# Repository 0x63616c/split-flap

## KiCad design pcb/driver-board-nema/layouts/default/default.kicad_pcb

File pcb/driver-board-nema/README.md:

# split-flap driver board v2 — NEMA 14 / TMC2209

Single-module driver for the split-flap: a socketed **Seeed XIAO ESP32-C6**
drives a socketed **TMC2209 SilentStepStick**, which drives a 4-lead bipolar
**NEMA 14** (0.6 A/phase, 1.8°). The whole module — motor, logic and hall
sensor — runs from **one 12 V barrel jack**.

62 × 76 mm, 2-layer, 1.6 mm FR4. Fits behind a module with room to spare
(the unit plate is 95 × 118 mm).

v1 (`../driver-board/`) is the 28BYJ-48 board — it drove a ULN2003 off USB 5 V.
This is a separate design, not a revision of it. (v1 has had exactly one change
made to it since: its XIAO socket was the same male-header part as this board's
was, and was swapped for a female receptacle.)

## Pinout

XIAO pin assignment is the one `firmware/micropython-spike/tmc_spin.py`
already uses. The hall wiring is carried over from the v1 bench, with a 1 kΩ
series resistor added.

| XIAO | Signal | Goes to |
|---|---|---|
| D0 | STEP | StepStick pin 10 |
| D1 | DIR | StepStick pin 9 |
| D2 | EN | StepStick pin 16 (active **low**; the module pulls it up, so the driver is off until firmware drives it) |
| D6 | PDN_UART | StepStick pin 11, through a 1 kΩ series resistor (R8) |
| D7 | PDN_UART **read** | the same net as D6. D7 is GPIO17 = U0RXD, so the UART can be read as well as written |
| D8 | HALL DO | J1 pin 3, through a 1 kΩ series resistor (R9) |
| 5V | +5 V in | fed **by the on-board buck** through D2, not by USB |
| 3V3 | +3.3 V out | StepStick VIO — this is what sets the driver's logic level |

D3/D4/D5/D9/D10 are socketed but unrouted.

> **The hall line floats when no magnet is present.** An open-collector
> output is high-Z when it is not pulling down, and nothing on this board
> pulls it up. Firmware **must** enable the XIAO's internal pull-up on D8 or
> it will read noise.

### StepStick socket (J5 = pins 9–16, J4 = pins 1–8)

Pin numbering follows the Trinamic *TMC2209 SilentStepStick* hardware manual
(doc rev 1.20). Note this is **not** the naive A4988 column order — the coils
are on the same side as VM, and the header does not carry DIAG or INDEX (those
are module pads 17/18).

```
J4 (pins 1-8)   GND  VIO  M1B  M1A  M2A  M2B  GND  VM
J5 (pins 9-16)  DIR  STEP PDN  UART SPRD MS2  MS1  EN
```

MS1, MS2 and SPREAD are tied to GND: UART address 0 and StealthChop.
Microstepping and run current are set over UART, not by jumpers.

Pin 12 (UART) is left unconnected. The reason is **not** that the module has
its own series resistor on it — it does not; the SilentStepStick fits a 20 kΩ
**pull-down** (R1) there. The reason is that pins 11 and 12 are the two ends
of the module's 3-way solder jumper JMP, and our 1 kΩ (R8) already provides
the series resistance the single-wire UART needs. Driving both ends would
just fight the jumper.

> ### ⚠ Bridge JMP to PDN before UART will do anything
>
> The SilentStepStick ships with **neither** side of JMP bridged: JMP.1 goes
> to pin 11 (PDN) and JMP.3 to pin 12 (UART), and out of the factory the pad
> is open. Until you bridge JMP to the **PDN** side, the driver never sees
> anything the XIAO sends — it silently runs STEP/DIR at its default 1/8
> microstep with the current set by the on-board trim pot, and every UART
> write is a no-op with no error.

### Connectors

| Ref | Type | Pinout (left → right as silkscreened) |
|---|---|---|
| J3 | 5.5 × 2.1 mm barrel, 3 A | **centre positive**, 12 V — **meter tip/sleeve before first power-up**, see below |
| J2 | JST-XH 4-pin, right angle | `A2 A1 B2 B1` — the connector is rotated, hence the reversed order. Labels follow the **driver's** coil naming: on a SilentStepStick M1 is coil B and M2 is coil A, so J2's `A` pair goes to the driver's M2 |
| J1 | JST-XH 3-pin, vertical | `5V GND DO` |

> **Meter J3's tip and sleeve before you apply 12 V.** DC-005 pad numbering is
> not standardised between vendors, and the two pads of the rear row are
> geometrically identical, so there is nothing to tell them apart by eye. The
> pin functions in `parts/DC_005C/DC_005C.ato` are derived by structural
> correspondence with the previous jack, not read off a datasheet — sound
> reasoning, but still an inference. Put a meter on a plugged-in barrel
> connector and confirm tip → J3 pad 1 and sleeve → J3 pad 2 first.

## Power

```
12V jack ──> Q1 (P-FET reverse-polarity gate) ──> +12V rail
                                                   ├─> StepStick VM  (C6 470uF + C7 22uF + C10 100nF)
                                                   └─> U1 TPS563201 ──> +5V ─┬─> hall sensor
                                                                             └─> D2 ──> XIAO 5V pad
XIAO 3V3 out ──> StepStick VIO
```

**Budget** — a 12 V ≥ 2 A brick covers it with margin:

| Load | Draw |
|---|---|
| Motor, 2 phases × 0.6 A into the coils | ~6–9 W → **0.5–0.75 A** at 12 V (coil resistance not in the listing; assumed 8–12 Ω — measure it) |
| XIAO ESP32-C6 (WiFi peaks) | ~0.5 A at 5 V → ~0.25 A at 12 V |
| Hall module | ~20 mA at 5 V |
| **Total** | **~1.0–1.3 A at 12 V** |

J3 is a DC-005C-20A, rated **3 A**. The 1 A-rated DC-005 this board first used
was at or over its limit continuously against that budget.

**VM bulk.** C6 is 470 µF / 25 V with 80 mΩ ESR and an 850 mA ripple rating,
sitting directly beside the StepStick's VM pin, with a 22 µF ceramic (C7)
alongside it for the mid-band and a 100 nF (C10) 2.5 mm from the VM pad itself
for the high-frequency edge — neither of the larger parts is a short at the
tens-of-MHz edges the TMC2209's gate drive puts on VM. The TMC2209 chops the
full coil current out of VM; undersizing this is the classic way to kill the
driver.

**Reverse polarity.** Worth it — barrel bricks vary and the TMC2209 does not
survive reverse VM. A high-side P-FET rather than a series Schottky: the diode
would drop ~0.4 V and burn ~0.4 W at 1 A, and eat the buck's headroom, where
the FET is ~50 mΩ (≈50 mV).

*Orientation.* A P-FET's body diode conducts **drain → source**, so for this to
block on reverse input the drain has to face the jack and the source the
protected rail — which is how Q1 is wired. Getting it the other way round is
not a no-op, it quietly defeats the whole circuit: with the source on the jack
side the body diode's anode faces the load, stays forward-biased under reverse
input, and conducts anyway, putting roughly **−11.3 V** across C6. An earlier
revision of this board had exactly that.

*Gate.* Not tied to GND — the AO3401A is only rated V<sub>GS</sub> ±12 V, which
a 12 V brick sits right on. R5/R6 (100 k/56 k) hang off the **source** (the
gate is referenced to the source, so the divider follows that pin) and park the
gate at 0.64 × V<sub>source</sub> below it: −7.7 V at 12 V in, −9.6 V even at a
15 V brick. Fully enhanced, safely inside the rating. On power-up the body
diode pulls the rail to V<sub>in</sub> − 0.7, which is what gives the divider a
live source to work from; the drop then collapses to I × R<sub>DS(on)</sub>.

**Buck.** TPS563201, 4.5–17 V in, 3 A, D-CAP2 — no external compensation and
no catch diode. V<sub>out</sub> = 0.768 × (1 + 54.9 k/10 k) = **4.99 V**.

*Cff.* R3 carries a 100 pF C0G in parallel (C9). A high-V<sub>out</sub> D-CAP2
converter on an all-ceramic output has very little phase margin at crossover;
TI's SLVAF45, *Why We Need Cff in High Output Voltage D-CAP2/3 Converter for
Stability*, works this exact 12 V → 5 V case and measures phase margin going
from **17.2° to 75.4°** once Cff is fitted. The 54.9 k/10 k pair is TI's from
that note, which is why it is 54.9 k and not 56 k.

*Output capacitance.* TI's stable window is 20–68 µF **effective**. A 22 µF
25 V X5R 0805 loses roughly half its value to DC bias at 5 V, so the two caps
this board originally carried gave ~20–24 µF — sitting on the floor of the
window with tolerance and temperature able to push it under. There are now
three (C3/C4/C8), for ~30–36 µF derated.

*EN.* A plain 100 k pull-up to the 12 V rail. Earlier revisions fitted a
100 k/56 k divider justified as a level-shift for a 6 V abs-max on EN; that
was wrong — SLVSD90B rates EN at abs-max **19 V**. It was not a useful UVLO
either (it releases at V<sub>in</sub> ≈ 3.3 V, below the part's own 4.5 V
minimum), so the low side is gone.

**Trace widths.** Motor coils, the 12 V spine and VM run at 1.0 mm; 5 V and
the buck power nets at 0.8 mm (0.6 mm where they escape the SOT-23-6); logic
at 0.4 mm. 1.0 mm on 1 oz outer copper carries ~2.5 A at a 10 °C rise, against
a ~0.85 A peak coil current.

**12 V and USB together.** The XIAO ESP32-C6's 5V pad is the *same net* as its
USB VBUS, with no series diode anywhere on the module (Seeed schematic v1.0).
Wired straight through, plugging in USB while 12 V was applied would have the
buck driving the host PC's VBUS rail backwards down the cable. **D2**, a
B5819W Schottky, makes that path one-way, so both supplies may be present at
once.

D2 sits between the buck and the socket *only*. Everything else on the board —
including the hall connector — taps the rail upstream of it, because the A3144
wants ≥ 4.5 V and would be marginal at 4.99 − 0.3 = 4.69 V. The XIAO's own
regulator is perfectly happy at 4.69 V.

## What to order

`fab-splitflap-driver-nema-v2.zip` → PCBWay, 2-layer, 1.6 mm FR4, HASL or ENIG,
any colour. It conforms comfortably to their standard 2-layer capability:

| Constraint | PCBWay standard | This board |
|---|---|---|
| Min trace / space | 6 mil (0.152 mm) | **15.7 mil (0.4 mm)** trace, 0.2 mm space |
| Min drill | 0.3 mm | **0.3 mm** (vias); smallest THT 0.8 mm |
| Min annular ring | 0.13 mm | **0.15 mm** |
| Min silkscreen width | 0.15 mm | **0.15 mm** — normalised at place time |
| Solder mask expansion | — | 0.05 mm |
| Board thickness | 1.6 mm | 1.6 mm |
| Layers | 2 | 2 |
| Outline | — | 62 × 76 mm, four 3.2 mm M3 holes |

The four M3 mounting holes are real **NPTH pads**, so they appear in
`filled-NPTH.drl` and get drilled to drill tolerance. They used to be inner
Edge.Cuts circles: a fab does cut those, but the non-plated drill file came out
empty, so nothing in the package actually declared them as holes.

Components: `bom.csv` — every part is LCSC-stocked and pinned by part number.
The three items under *not fitted* (StepStick, XIAO, 12 V PSU) are ordered
separately; the XIAO and StepStick plug into sockets and are not soldered down.

## Assembly notes

Everything is hand-solderable: 0603/0805 passives, SOT-23 and SOT-23-6, and
through-hole connectors. Suggested order — SMD first, tallest THT last:

1. **U1 (TPS563201)** and **Q1** — easiest with nothing else in the way.
2. 0603/0805 passives. **C6 (470 µF) is polarised**: pin 1 is +, and the
   footprint now prints a `+` beside pin 1 and a `−` beside pin 2, clear of
   the can. **D1** (LED) and **D2** (Schottky) are polarised too; both carry
   a printed cathode bar at their pin-1 end.
3. Sockets J4–J7 (**female** receptacles — the modules bring the male pins).
   Seat them square; a tilted socket makes the modules sit crooked. The two
   sockets do **not** share a row spacing:
   - **XIAO J6/J7 — 15.24 mm** (0.6 in). The module's pin rows really are
     0.6 in apart.
   - **StepStick J4/J5 — 12.70 mm** (0.5 in). The 0.6 × 0.8 in figure quoted
     for a StepStick is its *board outline*; the pin rows are inset 1.27 mm
     from each long edge, so centre-to-centre is 15.24 − 2 × 1.27. A first
     spin of this board used 15.24 mm here and the module would not seat.
     `tools/place_and_render.py` now asserts both pitches at place time.
4. Connectors J1, J2, J3 last.

Then, before plugging anything in:

- Apply 12 V and check **D1 lights** and the XIAO's 5V pin reads ~5.05 V.
- Confirm 3V3 is live on the socket before inserting the StepStick — VIO comes
  from the XIAO, so the driver must never be powered without the XIAO fitted.
- **Set the StepStick's V<sub>ref</sub> pot before running the motor.** The
  board does not break V<sub>ref</sub> out; use the module's own trim pot and
  creep the current up from minimum, per the note in `tmc_spin.py`. On a Watterott-style
  module (0.11 Ω sense, 1.77 A RMS at full scale) 0.6 A/phase RMS works out at
  V<sub>ref</sub> ≈ 0.85 V — but clones vary in sense resistor, so verify
  against your module before trusting that number.
- Insert the StepStick with **pin 1 / pin 9 at the end marked on the silk**.
  Both rows are identical 1×8 headers, so the arrow and the row labels
  (`J4 VM + COILS`, `J5 LOGIC`) are the only thing stopping a 180° insertion,
  which is destructive.
- **Bridge the StepStick's JMP jumper to the PDN side** if you want UART. See
  the note under *StepStick socket* above — it is unbridged from the factory
  and UART does nothing at all until you bridge it.
- **C6 is polarised and the can's own marking is counter-intuitive.** The
  footprint's chamfer marks the **positive** end (SamYoung BXJ case J10: the
  seating-plate bottom view puts the two chamfered corners on the (+) side,
  while the can-top's solid black band marks (−)). That is the opposite of
  what you get reading the stripe on the physical part. Go by the `+` glyph
  printed on the silk at C6's west end, or by pad 1.

## Building this from source

```
ato build                                    # twice after adding a component
tools/build_outputs.sh                       # place, route, DRC, renders, fab
tools/build_outputs.sh --quick               # place + DRC only
```

Placement and routing are address-keyed data tables in
`tools/place_and_render.py`, so they survive designator reshuffles. It also
self-checks placement numerically (body overlap, off-board, pad-to-pad) before
writing anything.

atopile's cloud registry was down, so all parts are vendored locally:
`tools/vendor_part.py <LCSC> <DIR>` (easyeda2kicad → faebryk `kicad.convert`).

> `tools/trim_lib_silk.py` is kept only for reference. **Do not run it.**
> Despite its docstring it is not idempotent: each run shrinks every stroke
> again, eroding silk on footprints it was never aimed at and desyncing the
> libraries from the layout. `../tools/verify_fab.py` reports silk that
> actually lands in a mask opening, with the depth, so the handful that
> matter can be fixed by hand.

A vendored footprint needs three things adding by hand before it is fab-ready:
an **F.CrtYd courtyard** (EasyEDA emits none, and KiCad's courtyard checks are
ignored by default, so nothing complains), a **body outline on F.SilkS** (the
connector parts draw theirs on F.Fab, which is not manufactured), and a
**polarity marker outside the body** if the part is polarised.

### DRC status

> ### ⚠ Do not run DRC on `layouts/default/default.kicad_pcb`
>
> That file is atopile's, and it ships with the GND zones **unfilled**. Running
> `kicad-cli pcb drc` directly on it reports **27 unconnected items and 8
> dangling vias — every one of them false**, because the pour that connects
> them has not been filled yet. Two reviewers and an orchestrator have each
> independently fallen into this.
>
> The real board is `build/filled.kicad_pcb`, which `tools/build_outputs.sh`
> derives by filling the zones with `--refill-zones`. DRC, gerbers, drill and
> renders all come from that copy. Just run `tools/build_outputs.sh`.

**0 errors, 0 unconnected pads, 0 footprint errors.**

The build promotes KiCad's courtyard rules to errors in
`build/filled.kicad_pro`. `missing_courtyard` and `courtyards_overlap` ship as
*ignored* checks — so for most of this board's life the body-overlap check was
being **skipped, not passed**, on 30 of 34 footprints. Every footprint now
carries a courtyard, the checks run, and they pass. `../tools/verify_fab.py`
re-derives the same conclusions from the exported board independently, and
also checks board extents, silk width and silk over mask openings.

Four warnings remain, all the same one:

```
[silk_overlap] @(40.6, 31.3):    Reference field of C8
               @(45.885, 35.325): Segment of C8 on F.Silkscreen
```

Spurious, and re-confirmed as such. The two items are 5.2 mm apart, and moving
C8's reference field ~24 mm away leaves all four warnings byte-for-byte
identical apart from the reported coordinate of the field itself — the
*clearance* it claims to have found does not track the geometry at all. It is the same KiCad text-extent mis-attribution recorded
against C4 on the v1 board, where DRC blames the wrong field. Nothing on the
silkscreen actually collides; compare `render/top.png`.

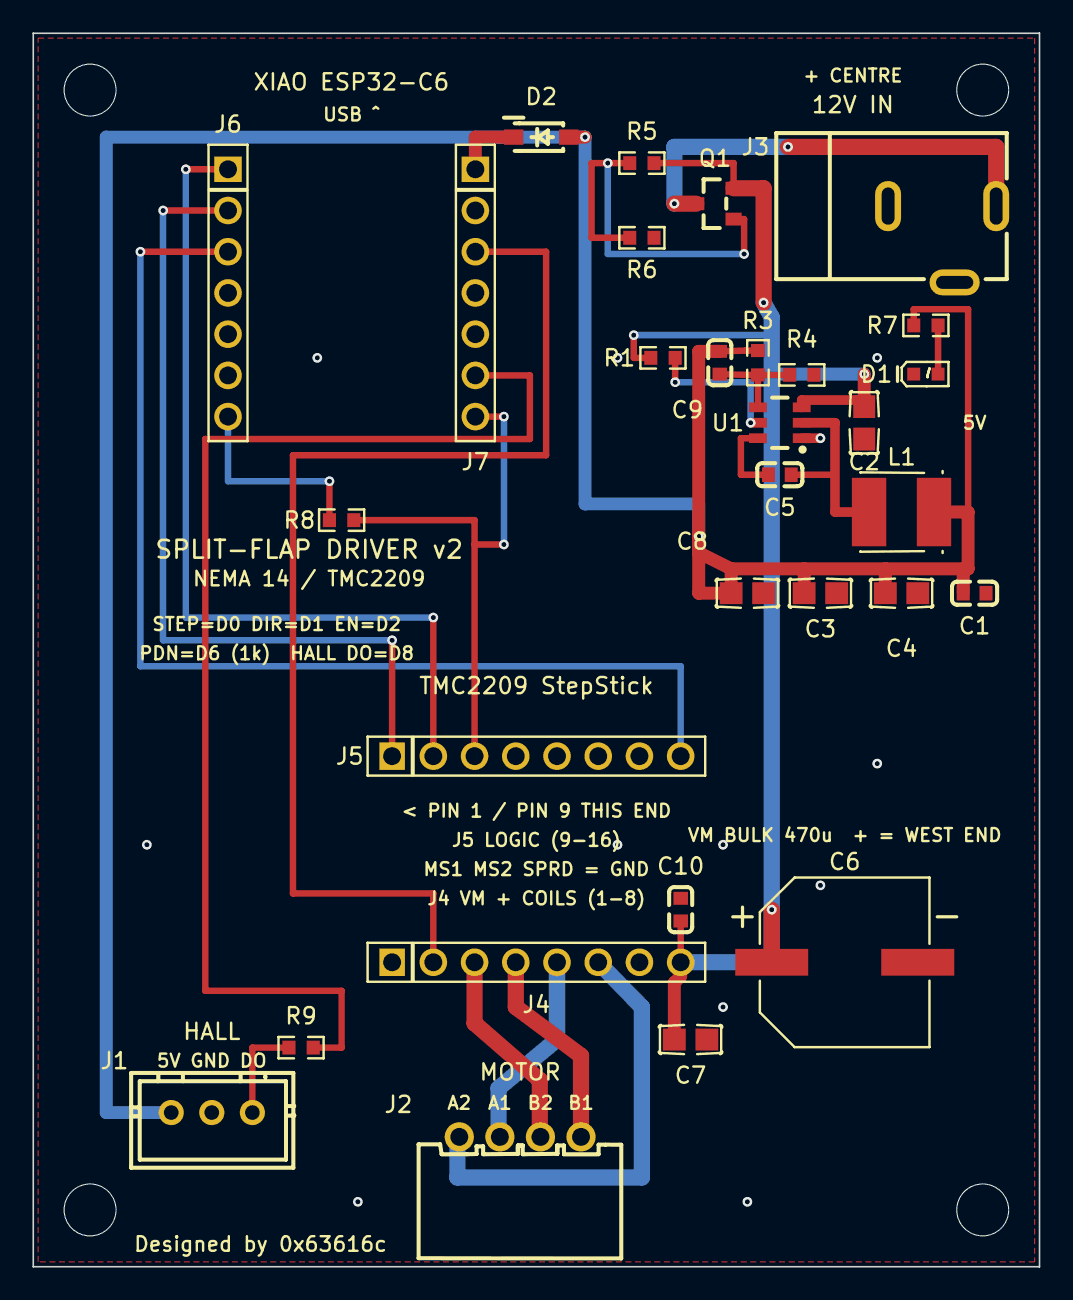
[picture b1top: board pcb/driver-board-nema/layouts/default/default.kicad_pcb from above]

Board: 2 copper layers, 62.0 x 76.0 mm, 30 parts (0 on the bottom side), 23 nets.

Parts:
C1, C5, C9, C10: C0603
C2, C3, C4, C7, C8: C0805
C6: CAP-SMD_BD10.0-L10.3-W10.3-LS11.0-FD
D1: LED0603-RD
D2: SOD-123_L2.7-W1.6-LS3.7-RD-1
J1: CONN-TH_3P-P2.50_A2501WV2-3P
J2: CONN-TH_XH2.54-4AW
J3: DC-IN-TH_DC-005C-20A
J4, J5: HDR-TH_8P-P2.54-V-F
J6, J7: HDR-TH_7P-P2.54-V-F
L1: IND-SMD_L5.0-W5.0
Q1: SOT-23_L2.9-W1.3-P1.90-LS2.4-BR
R1, R3, R4, R5, R6, R7, R8, R9: R0603
U1: SOT-23-6_L2.9-W1.6-P0.95-LS2.8-BR

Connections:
1: C1.1, C3.1, C4.1, C8.1, C9.1, D2.2, J1.1, L1.1, R3.1, R7.1
1-1: C2.1, C6.1, C7.1, C10.1, J4.8, Q1.2, R1.1, R5.2, U1.3
1-2: Q1.1, R5.1, R6.1
1-3: J6.7, R8.1
2: C1.2, C2.2, C3.2, C4.2, C6.2, C7.2, C8.2, C10.2, D1.1, J1.2, J3.2, J3.3, J4.1, J4.7, J5.5, J5.6, J5.7, J7.2, R4.2, R6.2, U1.1
2-1: C5.2, L1.2, U1.2
2-2: D1.2, R7.2
dir: J5.1, J6.2
en_n: J5.8, J6.3
hall_do: J7.6, R9.2
hall_raw: J1.3, R9.1
m1a: J2.1, J4.4
m1b: J2.2, J4.3
m2a: J2.3, J4.5
m2b: J2.4, J4.6
p3v3: J4.2, J7.3
p5v_xiao: D2.1, J7.1
pdn: J5.3, J7.7, R8.2
step: J5.2, J6.1
v12_raw: J3.1, Q1.3
vbst: C5.1, U1.6
ven: R1.2, U1.5
vfb: C9.2, R3.2, R4.1, U1.4

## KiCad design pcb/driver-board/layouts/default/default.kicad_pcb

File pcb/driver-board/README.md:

# split-flap driver board v1 — 28BYJ-48 / ULN2003

Single-module driver for the split-flap: a socketed **Seeed XIAO ESP32-C6**
drives a **ULN2003** Darlington array, which drives a 5-wire unipolar
**28BYJ-48** off USB 5 V. A 3-pin header takes the hall sensor.

45 × 60 mm, 2-layer, 1.6 mm FR4.

v2 (`../driver-board-nema/`) is the NEMA 14 / TMC2209 board — a separate
design, not a revision of this one.

## Pinout

| XIAO | Signal | Goes to |
|---|---|---|
| D0–D3 | IN1–IN4 | ULN2003 inputs |
| D8 | HALL DO | J1 pin 3 |
| 5V | +5 V | ULN2003 COM (the coils' flyback clamp rail) and J2 pin 5 |

D9/D10 are socketed but unrouted.

> **The hall line floats when no magnet is present.** An open-collector output
> is high-Z when it is not pulling down, and nothing on this board pulls it
> up. Firmware **must** enable the XIAO's internal pull-up on D8 or it will
> read noise.

### Connectors

| Ref | Type | Pinout |
|---|---|---|
| J2 | JST-XH 5-pin | 28BYJ-48 motor. Pins 1–4 are OUT1–OUT4; pin 5 is the motor common (red wire), marked `+5V` on the silk |
| J1 | JST-XH 3-pin, vertical | `5V GND DO` — hall sensor |
| J3 / J4 | 1×7 female receptacles, **15.24 mm apart** | XIAO socket — the module brings the male pins |

## Assembly notes

SMD first, tallest through-hole last:

1. **U1 (ULN2003, SOIC-16)** — easiest with nothing else in the way.
2. **C1 (220 µF) is polarised**: pin 1 is **+**. There is a `+` and a `−` on
   the silk just outside the can at each end, as well as the original pair
   under the body (which you cannot see once the part is fitted).
3. Sockets J3/J4 (**female** receptacles). Seat them square; a tilted socket
   makes the module sit crooked.
4. Connectors J1, J2 last.

The four M3 mounting holes are real **NPTH pads**, so they appear in
`filled-NPTH.drl` and get drilled to drill tolerance. They used to be inner
Edge.Cuts circles: a fab does cut those, but the non-plated drill file came
out empty, so nothing in the package actually declared them as holes.

## What to order

`fab-splitflap-driver-v1.zip` → PCBWay, 2-layer, 1.6 mm FR4, HASL or ENIG,
any colour. Components: `fab/bom.csv` — every part is LCSC-stocked and pinned
by part number. The XIAO plugs into its socket and is not soldered down.

## Building this from source

```
ato build                                    # twice after adding a component
tools/build_outputs.sh                       # place, route, DRC, renders, fab
tools/build_outputs.sh --quick               # place + DRC only
```

Placement and routing are address-keyed data tables in
`tools/place_and_render.py`, so they survive designator reshuffles. It
self-checks placement numerically (body/courtyard overlap, off-board,
pad-to-pad) and normalises every silk stroke to PCBWay's 0.15 mm minimum
before writing anything.

### DRC status

> ### ⚠ DRC the derived board, not `layouts/`
>
> `layouts/default/default.kicad_pcb` is atopile's, and `kicad-cli
> --save-board` rewrites it in a dialect faebryk's parser rejects. The real
> board is `build/filled.kicad_pcb`, which `tools/build_outputs.sh` derives;
> DRC, gerbers, drill, placement and renders all come from that copy. Just run
> `tools/build_outputs.sh`.

**0 errors, 0 warnings, 0 unconnected pads, 0 footprint errors.**

The build also promotes KiCad's courtyard rules. `missing_courtyard` and
`courtyards_overlap` ship as *ignored* checks, which means a board with no
courtyards at all passes cleanly while the body-overlap check never runs.
`build/filled.kicad_pro` turns both into errors, and `../tools/verify_fab.py`
independently re-checks courtyards, board extents, silk width and
silk-over-mask-opening numerically on the exported board.

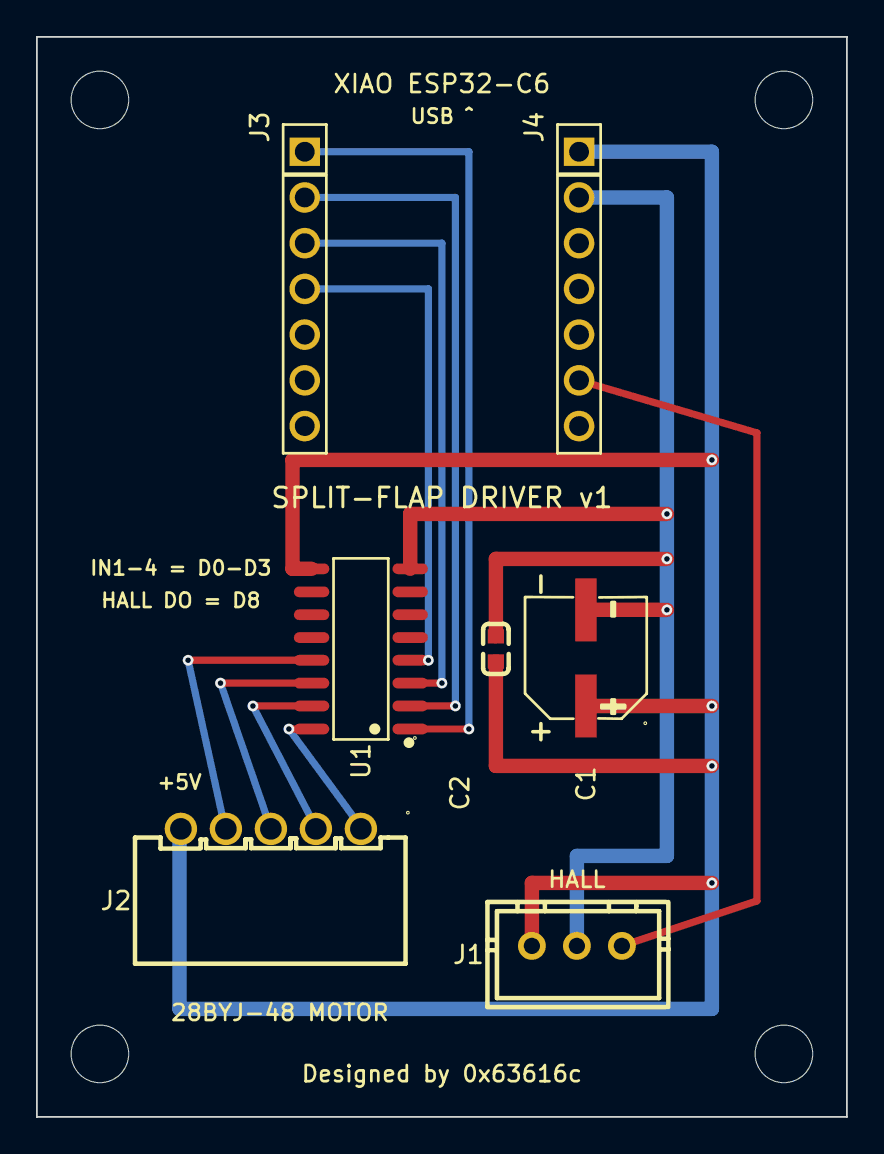
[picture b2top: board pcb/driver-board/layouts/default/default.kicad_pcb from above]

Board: 2 copper layers, 45.0 x 60.0 mm, 7 parts (0 on the bottom side), 11 nets.

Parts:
C1: CAP-SMD_BD6.3-L6.6-W6.6-FD
C2: C0603
J1: CONN-TH_3P-P2.50_A2501WV2-3P
J2: CONN-TH_XH2.54-5AW
J3, J4: HDR-TH_7P-P2.54-V-F
U1: SOIC-16_L9.9-W3.9-P1.27-LS6.0-BL

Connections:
1: C1.1, C2.1, J1.1, J2.5, J4.1, U1.9
1-1: J3.1, U1.1
1-2: J2.1, U1.16
2: C1.2, C2.2, J1.2, J4.2, U1.8
2-1: J3.2, U1.2
3: J3.3, U1.3
4: J3.4, U1.4
13: J2.4, U1.13
14: J2.3, U1.14
15: J2.2, U1.15
hall_do: J1.3, J4.6
